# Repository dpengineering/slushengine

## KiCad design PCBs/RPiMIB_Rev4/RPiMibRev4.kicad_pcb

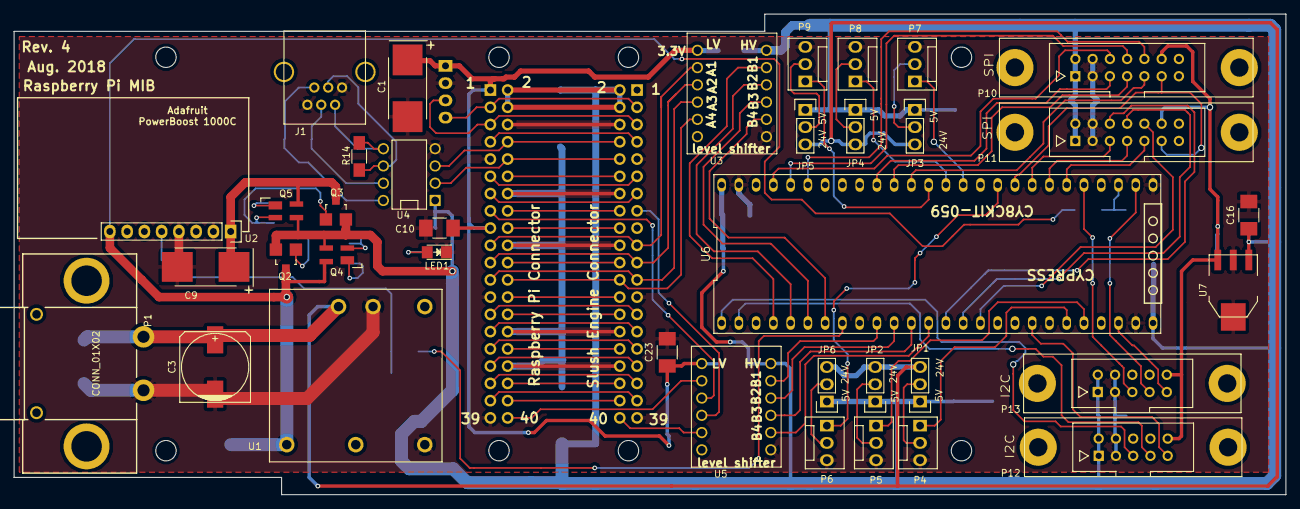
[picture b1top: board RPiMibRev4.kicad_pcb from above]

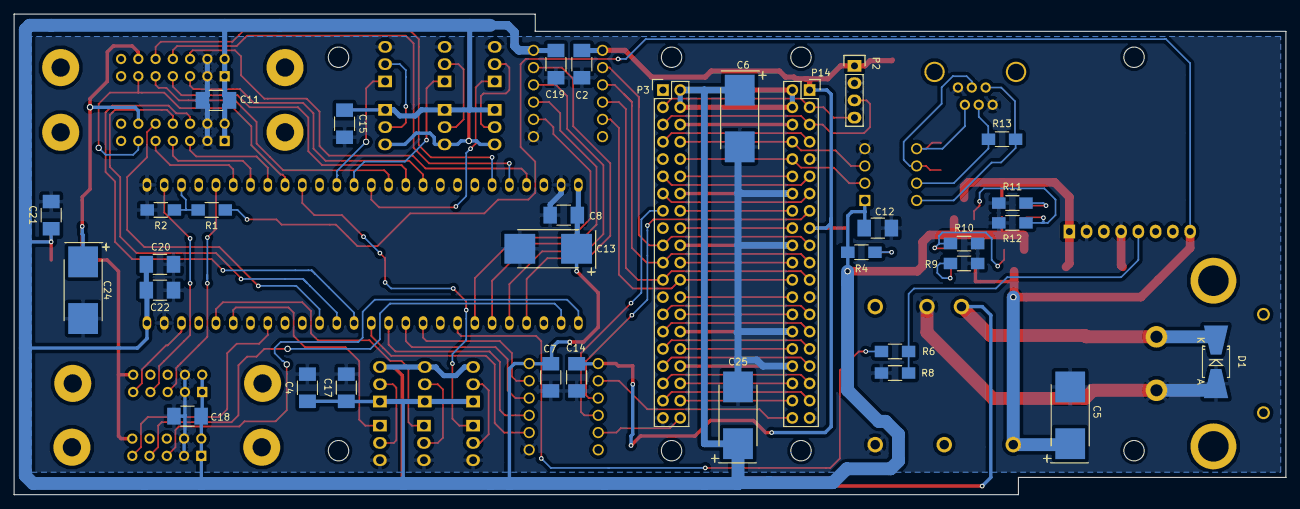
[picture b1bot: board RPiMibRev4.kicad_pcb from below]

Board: 2 copper layers, 187.2 x 70.7 mm, 70 parts (33 on the bottom side), 88 nets.

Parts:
C1, C5, C6, C9, C13, C24, C25: 10uF; TantalC_SizeE_EIA-7360_HandSoldering
C2, C4, C7, C8, C10, C11, C12, C14, C15, C16, C17, C18, C19, C20, C21, C22, C23: 0.1uF; C_1210_HandSoldering
C3: 220uF; c_elec_10x10
D1: D; SMB-SMC_Universal_Handsoldering
J1: RJ12; RJ12_E
JP1, JP2, JP3, JP4, JP5, JP6: Jumper_NC_Dual; Pin_Header_Straight_1x03
LED1: LED; LED-1206
P1: CONN_01X02; ANDERSON_POWERPOLE_1X2_RA_WINGS
P2: Raspberry_Pi_+_Conn; Socket_Strip_Straight_2x20
P3: Raspberry_Pi_+_Conn; Pin_Header_Straight_2x20
P4, P5, P6, P7, P8, P9: CONN_01X03; Pin_Header_Keyed_1x03
P10, P11: CONN_02X07; he10-14d
P12, P13: CONN_02X05; he10-10d
P14: CONN_01X04; Pin_Header_Straight_1x04
Q2, Q3: DMG2305UX; SOT-23
Q4, Q5: BCV62; SOT-143_Handsoldering
R1: 30K; R_1206_HandSoldering
R2, R6: 1.0K; R_1206_HandSoldering
R4: 510; R_1206_HandSoldering
R8, R9, R11: 10K; R_1206_HandSoldering
R10, R12: 47K; R_1206_HandSoldering
R13, R14: 51; R_1206_HandSoldering
U1: PDQ30-Q24-S5-D; pdq30
U2: PowerBoost 1000; Socket_Strip_Straight_1x08
U3, U5: ADAFRUIT_TXB0104
U4: MAX488; DIP-8__300
U6: PSOC_5LP; DIP-52_1_ELL
U7: LT1129CST-3.3; SOT-223

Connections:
+3.3VA: C24.1, P10.12, P11.12, P12.10, P13.10, U7.3
+3V3: C1.1, C2.1, C10.1, C14.1, C23.1, P2.1, P2.17, P14.1, U3.1, U5.1
+5V: C4.1, C6.1, C7.1, C8.1, C11.1, C12.1, C13.1, C15.1, C16.1, C17.1, C18.1, C19.1, C20.1, C21.1, C22.1, C25.1, JP1.1, JP2.1, JP3.1, JP4.1, JP5.1, JP6.1, P2.2, P2.4, P3.2, P3.4, P10.1, P10.2, P11.1, P11.2, P12.1, P12.2, P13.1, P13.2, Q2.2, Q3.2, Q4.3, Q5.3, R4.1, U3.12, U4.1, U5.12, U6.26, U6.52, U7.1
/IDEAL_DIODE_1/ANODE: C5.1, Q2.3, Q4.4, R1.1, U1.3, U2.8
/IDEAL_DIODE_2/ANODE: C9.1, Q3.3, Q5.4, U2.1
/INT_1: P12.9, U6.19
/INT_2: P13.9, U6.24
/MISO_1: P11.5, U6.34
/MOSI_1: P11.7, U6.33
/RESET: P10.11, P11.11, U6.35
/Rpi_miso: U3.10, U6.5
/Rpi_mosi: U3.11, U6.4
/Rpi_sclk: U3.9, U6.6
/Rpi_ss: U3.8, U6.7
/SCLK_1: P11.9, U6.32
/SCL_1: P12.7, U6.2
/SCL_2: P13.7, U6.28
/SDA_1: P12.5, U6.1
/SDA_2: P13.5, U6.31
/Supply_monitor: R1.2, R2.1, U6.29
/cs_1a: P11.6, U6.14
/cs_1b: P11.8, U6.15
/cs_1c: P11.10, U6.16
/cs_a: P10.6, U6.49
/cs_b: P10.8, U6.48
/cs_c: P10.10, U6.47
/enable_battery: R6.2, U6.8
/miso: P10.5, U6.43
/mosi: P10.7, U6.42
/pwm_a: P4.1, U6.21
/pwm_b: P5.1, U6.22
/rpi_inta: U5.9, U6.12
/rpi_intb: U5.8, U6.13
/sar_in1: P6.1, U6.36
/sar_in2: P7.1, U6.38
/sar_in3: P8.1, U6.39
/sar_in4: P9.1, U6.40
/sclk: P10.9, U6.41
/slush_inta: U5.11, U6.10
/slush_intb: U5.10, U6.11
/v24in: C3.1, D1.1, JP1.3, JP2.3, JP3.3, JP4.3, JP5.3, JP6.3, P1.1, U1.1
GND: C1.2, C2.2, C3.2, C4.2, C5.2, C6.2, C7.2, C8.2, C9.2, C10.2, C11.2, C12.2, C13.2, C14.2, C15.2, C16.2, C17.2, C18.2, C19.2, C20.2, C21.2, C22.2, C23.2, C24.2, C25.2, D1.2, J1.1, J1.6, LED1.1, P1.2, P2.6, P2.9, P2.14, P2.20, P2.25, P2.30, P2.34, P2.39, P3.6, P3.9, P3.14, P3.20, P3.25, P3.30, P3.34, P3.39, P4.3, P5.3, P6.3, P7.3, P8.3, P9.3, P10.3, P10.4, P11.3, P11.4, P12.3, P12.4, P13.3, P13.4, P14.2, R2.2, R8.1, R9.2, R10.2, R11.2, R12.2, U1.2, U1.5, U2.2, U2.4, U3.7, U4.4, U5.7, U6.25, U6.27, U6.51, U7.2, U7.4
unnamed: J1.2, R13.2, U4.8
unnamed: J1.3, R13.1, U4.7
unnamed: J1.4, R14.2, U4.6
unnamed: J1.5, R14.1, U4.5
unnamed: JP1.2, P4.2
unnamed: JP2.2, P5.2
unnamed: JP3.2, P7.2
unnamed: JP4.2, P8.2
unnamed: JP5.2, P9.2
unnamed: JP6.2, P6.2
unnamed: LED1.2, R4.2
unnamed: P2.7, P3.7
unnamed: P2.8, P3.8, U4.3
unnamed: P2.10, P3.10, U4.2
unnamed: P2.11, P3.11
unnamed: P2.12, P3.12
unnamed: P2.13, P3.13
unnamed: P2.15, U5.3
unnamed: P2.16, P3.16
unnamed: P2.18, P3.18
unnamed: P2.19, P3.19, U3.2
unnamed: P2.21, P3.21, U3.3
unnamed: P2.22, P3.22
unnamed: P2.23, P3.23, U3.4
unnamed: P2.24, P3.24, U3.5
unnamed: P2.26, P3.26
unnamed: P2.27, P3.27
unnamed: P2.28, P3.28
unnamed: P2.29, P3.29
unnamed: P2.31, P3.31
unnamed: P2.32, P3.32
unnamed: P2.33, P3.33
unnamed: P2.35, P3.35
unnamed: P2.36, P3.36
unnamed: P2.37, P3.37
unnamed: P2.38, P3.38
unnamed: P2.40, U5.2
unnamed: P3.15, U5.4
unnamed: P3.40, U5.5
unnamed: P2.5, P3.5, P14.3
unnamed: P2.3, P3.3, P14.4
unnamed: Q2.1, Q4.2, R10.1
unnamed: Q3.1, Q5.2, R12.1
unnamed: Q4.1, R9.1
unnamed: Q5.1, R11.1
unnamed: R6.1, R8.2, U2.5

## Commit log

2018-03-21 fixed eror in sBoard.readInput()
2018-09-10 added check GPIO files
2018-09-25 Configured for Pull Up resistors on getIOState
2018-10-04 change the device of spi.open to 1
2018-10-10 Added comment on changing sBoard.spi.open(0,1)
2018-10-15 uploaded datasheet PDFs for L6470 and MCP23017
2018-10-16 better comments
2018-10-16 commented
2018-10-16 Update Board.py
    the best comments
2018-10-16 fixed weird editors thingy
2018-10-16 Slush I2C IO Breakout
    Schematic for the
2018-10-16 commented on motor.py
2018-10-16 added comments
2018-10-17 added some comments that might maybe help someone in the future perhaps
2018-10-17 h commented and cleaned up double_limit and limit_switch
2018-10-17 fixed typos
2018-10-17 added some comments properly this time
2018-10-17 .idea is gone
2018-10-18 PDF of Slush IO Breakout Board
2018-10-18 PDF of RPiMIB SPI Breakout Schematic
    PDF of RPiMIB SPI Breakout Schematic
2018-10-18 Image of Slush IO Breakout and RPiMIB Breakout
    Image of Slush IO Breakout and RPiMIB Breakout
2018-10-18 Image of Slush I2C IO Breakout Board
    Image of Slush I2C IO Breakout Board
2018-10-18 Slush I2C Breakout Board RRB
    Slush I2C Breakout Board RRB
2018-10-18 Slush IO SPI Breakout Board
    Slush IO SPI Breakout Board
2018-10-22 PDF of RPiMIB Rev3 Schematic
    PDF of RPiMIB Rev3 Schematic
2018-10-22 SCH file for RPiMIB Rev3 Schematic
    SCH file for RPiMIB Rev3 Schematic
2018-10-22 RPiMib Rev3 PCB layout KiCad file
    RPiMib Rev3 PCB layout KiCad file
2018-10-22 image of front of RPiMIB rev3 layout design
    image of front of RPiMIB rev3 layout design
2018-10-22 image of back of RPiMIB rev3 layout design
    image of back of RPiMIB rev3 layout design
2018-10-22 PDF of RPiMib rev 4 Schematic
    PDF of RPiMib rev 4 Schematic
2018-10-22 RPiMib Rev 4 Schematic SCH file
    RPiMib Rev 4 Schematic SCH file
2018-10-22 image of front of RPiMIB rev4 layout design
    image of front of RPiMIB rev4 layout design
2018-10-22 image of back of RPiMIB rev4 layout design
    image of back of RPiMIB rev4 layout design
2018-10-22 layout deisgn of RPiMIB rev 4 KiCad file
    layout deisgn of RPiMIB rev 4 KiCad file
2018-10-22 PDF of RPiMIB rev 2 Schematic
    PDF of RPiMIB rev 2 Schematic
2018-10-22 RPiMIB rev 2 Schmatic SCH file
    RPiMIB rev 2 Schmatic SCH file
2018-10-23 Moved files to individual folders
2018-10-23 Moving Files Around
2018-10-23 image of front of RPiMIB rev 2 layout design
    image of front of RPiMIB rev 2 layout design
2018-10-23 image of back of RPiMIB rev 2 layout design
    image of back of RPiMIB rev 2 layout design
2018-10-24 Bill of Materials for Slush I2C Breakout Board
    Bill of Materials for Slush I2C Breakout Board
2018-10-24 BOM for Slush IO Breakout
    BOM for Slush IO Breakout
2018-10-24 BOM for RPIMIB REV 4
    BOM for RPIMIB REV 4
2018-10-24 BOM for RPIMIB REV 2
    BOM for RPIMIB REV 2
2018-10-24 BOM for RPIMIB REV 3
    BOM for RPIMIB REV 3
2018-10-24 BOM for RPIMIB SPI Breakout
    BOM for RPIMIB SPI Breakout
2018-11-30 fixed temperature
2019-01-10 Added note about slush engine update to readInput
2019-01-15 Moved PCBs to RPiMIB from slushengine
2019-02-08 Fixed syntax issues
2019-02-28 added read to ioExpansioBoard Config in init
2019-02-28 fixed to correct i2c address
2019-03-01 Added ability to select board in sBoard constructor
2019-03-01 removed line that was used for testing
2019-03-01 Moved ioExpander into 'XLT' init
2019-03-01 Removed Temperature.py from Slush, this ability is no longer supported on Slush Engine boards. ADditionally we use our own temperature sensor
2019-03-18 Changed Default CONFIG register from 0x3608 to 0x3688 to enable OC_SD - this will shutdown driver if over-current is detected. Also updated for case when disabling SW_MODE - External switch hard stop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
2019-05-23 Created
2019-05-23 Updated All Registers to Match DataSheet
2019-05-23 Rounded up OCD_TH values to remove periods
2019-05-23 Created and tested with XLT
2019-05-23 updated board.py, motor.py, and L6470Registers.py
2019-05-23 Fixed and tested with Model D
2019-08-29 Updated motor.py to use correct Initialization
2019-08-29 updated to work with XLT by default. Model D projects use ModelDFix branch
2019-08-29 Fix typo in Motor.py
2019-10-11 Added SetSlope to init the Slope profiles of the stepper.
2019-11-22 Deploy dpengineering/slushengine to github.com/dpengineering/slushengine.git:gh-pages
2019-12-19 Added the ability to watch the Slush Engine Motor Flag Pin, as well as refactored/cleaned up Board.py and Motor.py. Created boardutilities.py to hold utilities used by board.py. Moved print_status fr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
    Changed gpio_callback. There is now a print_status in the HIGH debug level. Additionally, the way the script exits has been changed in the HIGH ebug level
    Refactors gpio_callback into flag_pin_callback() as a static method of Motor.py. Refactoring into a static method ensures that any motor that triggers an alert will be properly handled. Changed the b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
2019-12-20 Removed return if a Model D is being used. Dynamically sets the chip select list based upon the board being used.
2020-02-26 Removed chip monitoring
